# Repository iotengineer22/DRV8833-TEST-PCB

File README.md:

# PCB-DRV8833-TEST
DRV8833-PCB-KiCad-DATA

# Schematics

# Artwork

# BOM-List
Motor-Driver-PCB --- Original-PCB

Motor-Driver-IC(U1) --- DRV8833PWPR

Resistor_SMD(R1) --- 0603_1608Metric_10k

Resistor_SMD(R2.R3) --- 0603_1608Metric_0 (or short-bar)

Capacitor_SMD(C1) --- 0603_1608Metric_2.2u

Capacitor_SMD(C2) --- 0603_1608Metric_10u

Capacitor_SMD(C3) --- 0603_1608Metric_0.1u

PinHeader_2x06(J1) -- 2x06_P2.54mm_Horizontal

PinHeader_1x02(J2,J3,J4) --- 1x02_P2.54mm_Vertical

# PCB specifications
Zip the "drv8833-pcb" folder and send it to any PCB fabrication company (e.g., PCBGOGO).

The PCB specifications match the default settings of most fabrication companies. Just enter the dimensions and proceed with the order.

PCB Size: 17.78mm x 40.64mm

Layers: 2

Material: FR-4

FR4-TG: TG150-160

Thickness: 1.6mm

Min track/spacing: 6/6mil

Minimum hole size: 0.3mm

Solder mask: Green

Silkscreen: White

# DEMO

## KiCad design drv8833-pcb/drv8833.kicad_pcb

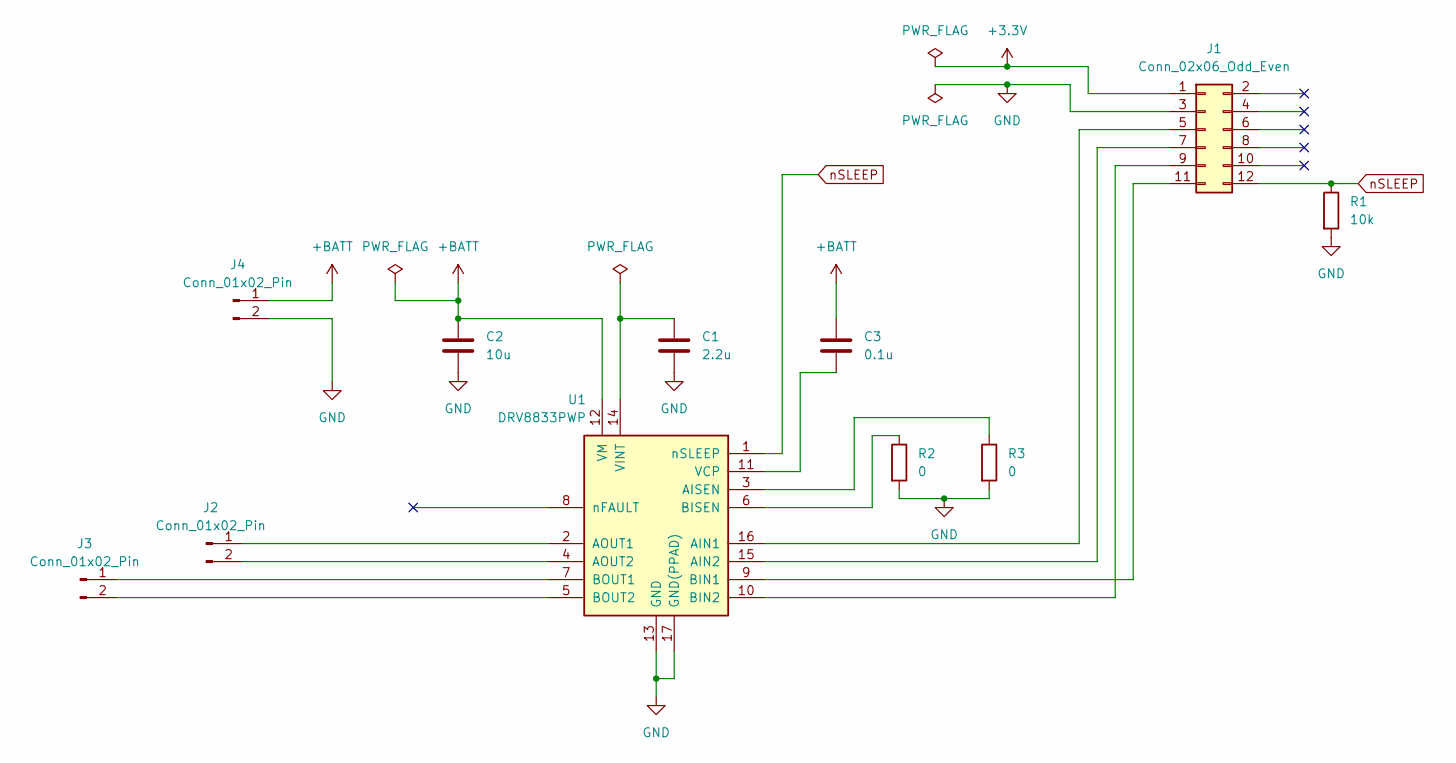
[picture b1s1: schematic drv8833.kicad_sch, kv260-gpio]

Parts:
C1: 2.2u; C_0603_1608Metric
C2: 10u; C_0603_1608Metric
C3: 0.1u; C_0603_1608Metric
J1: Conn_02x06_Odd_Even; PinHeader_2x06_P2.54mm_Horizontal
J2, J3, J4: Conn_01x02_Pin; PinHeader_1x02_P2.54mm_Vertical
R1: 10k; R_0603_1608Metric
R2, R3: 0; R_0603_1608Metric
U1: DRV8833PWP; HTSSOP-16-1EP_4.4x5mm_P0.65mm_EP3.4x5mm_Mask2.46x2.31mm_The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

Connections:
+3.3V: J1.1
+BATT: C2.1, C3.1, J4.1, U1.12 (VM)
GND: C1.2, C2.2, J1.3, J4.2, R1.2, R2.2, R3.2, U1.13 (GND), U1.17 (GND(PPAD))
unnamed: J1.5, U1.16 (AIN1)
unnamed: J1.7, U1.15 (AIN2)
unnamed: J1.9, U1.10 (BIN2)
unnamed: J1.11, U1.9 (BIN1)
unnamed: J2.1, U1.2 (AOUT1)
unnamed: J2.2, U1.4 (AOUT2)
unnamed: J3.1, U1.7 (BOUT1)
unnamed: J3.2, U1.5 (BOUT2)
unnamed: R3.1, U1.3 (AISEN)
unnamed: R2.1, U1.6 (BISEN)
unnamed: C3.2, U1.11 (VCP)
unnamed: C1.1, U1.14 (VINT)
nSLEEP: J1.12, R1.1, U1.1 (nSLEEP)

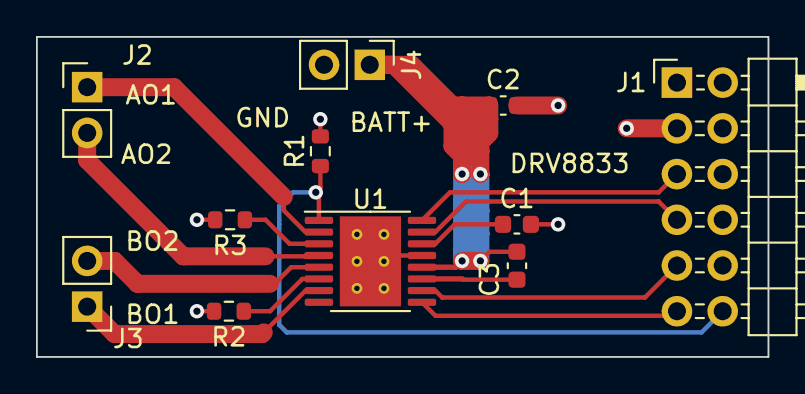
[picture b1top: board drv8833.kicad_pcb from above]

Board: 2 copper layers, 40.6 x 17.8 mm, 11 parts (0 on the bottom side), 15 nets.

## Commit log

2024-05-29 Add files via upload
    add images
2024-05-29 Update README.md
    add images
2024-05-29 Update README.md
    modify images
2024-06-03 Update README.md
    add BOM
